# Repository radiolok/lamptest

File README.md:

# lamptest

A modern MCU-based tester for vacuum tubes.

This repository is based on the Polish **AVT5229** vacuum tube tester
("Miernik lamp elektronowych", firmware "VTTester 1.16"). It contains:

* the AVR firmware, ported from the original ICCAVR sources to avr-gcc
* a KiCad 9 redraw of the schematic and PCB, with 3D models
* the original magazine article ([`AVT5229.pdf`](docs/AVT5229.pdf), in Polish) and its [English translation](docs/AVT5229_en.md)

| Top view | Schematic |
|---|---|
|  |  |

## Repository layout

```
firmware/             AVR firmware (C, avr-gcc)
  tests/              host unit tests, with fakes for the hardware
  avt5529.cproj       Atmel Studio 7 project
hardware/             KiCad 9 project: avt.kicad_sch, avt.kicad_pcb
  3d/                 STEP models referenced by the PCB
docs/
  AVT5229.pdf         original article (Polish)
  AVT5229_en.md       English translation
  images/             photos, article figures, PCB renders and diagrams
  diagrams/           diagram sources (make_diagrams.py)
cmake/                avr-gcc toolchain file
```

The PCB refers to the models in `hardware/3d/` as `${KIPRJMOD}/3d/...`, so the
project opens with its 3D view intact from any location. The README diagrams
are drawn by [`docs/diagrams/make_diagrams.py`](docs/diagrams/make_diagrams.py).
After editing it, run `python3 docs/diagrams/make_diagrams.py` to regenerate the
SVGs and the PNGs (it needs `rsvg-convert`, package `librsvg2-bin`).

## What it does

The tester applies the operating voltages from a tube's datasheet. It then
measures the tube's static parameters and its small-signal parameters:

| Quantity | Range | Resolution |
|---|---|---|
| Heater voltage U<sub>h</sub> (or heater current I<sub>h</sub> for series-heated P/U tubes) | 0–15.0 V / 0–2.50 A | 0.1 V / 10 mA |
| Grid bias −U<sub>g1</sub> | 0 … −24.0 V | 0.1 V |
| Anode voltage U<sub>a</sub> | 0–300 V | 1 V |
| Anode current I<sub>a</sub> (auto-range 20 / 200 mA) | 0–200.0 mA | 0.01 / 0.1 mA |
| Screen voltage U<sub>g2</sub> | 0–300 V | 1 V |
| Screen current I<sub>g2</sub> | 0–40.00 mA | 0.01 mA |
| Transconductance S = ΔI<sub>a</sub>/ΔU<sub>g1</sub> | 0–99.9 mA/V | 0.1 |
| Internal resistance R = ΔU<sub>a</sub>/ΔI<sub>a</sub> | 0–99.9 kΩ | 0.1 |
| Amplification factor K = S·R | 0–99.9 | 0.1 |

### Measurement sequence

The sequence runs in 250 ms ticks, driven by `TIMER2_COMP_vect`:

1. Switch on the heater, then wait out the warm-up time (1–9 min, set per tube).
2. Make U<sub>g1</sub> slightly more negative than U<sub>g</sub> (11 ADC steps, about 0.4 V), then ramp up U<sub>a</sub> and U<sub>g2</sub>. Read I<sub>a</sub> and U<sub>g1</sub>.
3. Make U<sub>g1</sub> the same amount less negative than U<sub>g</sub>, and read I<sub>a</sub> and U<sub>g1</sub> again. This gives **S**.
4. Return U<sub>g1</sub> to U<sub>g</sub>. Read I<sub>a</sub> at U<sub>a</sub> − 10 V and at U<sub>a</sub> + 10 V. This gives **R**, and **K** = S·R.
5. Latch the results on the LCD and send them over RS-232.
6. Ramp down U<sub>g2</sub>, U<sub>a</sub> and U<sub>g1</sub>, beep, and switch off the heater.

Press the knob to start a measurement. While the results are on screen, press it
again to re-measure without waiting for warm-up. Turn the knob to abort a
measurement or leave the results screen, which switches off the heater.

### Protections

* **Heater overcurrent**: the heater is switched off (`H` on the LCD).
* **Anode overcurrent** on the 200 mA range: U<sub>a</sub> and U<sub>g2</sub> are switched off (`A`).
* **Screen overcurrent**: U<sub>g2</sub> is switched off (`G`).
* **Heatsink over-temperature** (LM35 sensor): trips above 80 °C, clears below 70 °C (`T`).
* Any error aborts the measurement and sounds the buzzer.
* The watchdog timeout is about 1 s.

## Hardware

* **MCU**: ATmega32 with a 16 MHz crystal. The schematic symbol is the pin-compatible ATmega16A-P.
* **Display**: 4×20 HD44780 LCD in 4-bit mode.
* **Input**: rotary encoder with a push button, and a buzzer.
* **Heater supply**: a PWM step-down converter from the +15 V rail (OC0 → TC4426 → IRF9540N, 1 mH inductor, 1N5822). It runs in voltage mode, or in current mode for series-heater tubes.
* **U<sub>a</sub> and U<sub>g2</sub>**: two linear series regulators fed from a +335 V rail. A filtered PWM signal (OC1B, OC1A) sets the voltage, an LM358 drives an IRF740 pass transistor, and a BD139 limits the current. Their currents are measured on the high side with an LM358 and an MPSA94.
* **U<sub>g1</sub>**: negative bias from a charge pump, clocked by the MCU (`CKUG1`) through a TC4426. It is regulated sample-by-sample in the ADC ISR.
* **Relays**: one relay switches between anode sections (A1/A2). Another switches the I<sub>a</sub> shunt (20/200 mA).
* **Power**: a +15 V rail with a 10 000 µF reservoir capacitor, and an LM317 that makes +5 V for the logic.
* **Interface**: RS-232 through a MAX202, 9600 8N1.

### Block diagram

Blue arrows are control signals from the MCU, labelled with their pins. Dashed
orange arrows are the analog measurements that go to the ADC (port A). The red
tags show which supply rail feeds each block.

### MCU pinout

| Port | 7 | 6 | 5 | 4 | 3 | 2 | 1 | 0 |
|---|---|---|---|---|---|---|---|---|
| **A** (ADC) | U<sub>g1</sub> | I<sub>g2</sub> | U<sub>g2</sub> | I<sub>a</sub> | U<sub>a</sub> | U<sub>h</sub> | I<sub>h</sub> | Temp (LM35) |
| **B** | SCK | MISO | MOSI | K1 | U<sub>h</sub> PWM (OC0) | U<sub>g1</sub> pump clock | Anode select | I<sub>a</sub> range |
| **C** | LCD D7 | LCD D6 | LCD D5 | LCD D4 | LCD E | LCD RS | SDA | SCL |
| **D** | Buzzer (OC2) | Encoder DIR | U<sub>g2</sub> PWM (OC1A) | U<sub>a</sub> PWM (OC1B) | Encoder CLK (INT1) | Encoder button | TXD | RXD |

## Firmware structure

The firmware lives in [`firmware/`](firmware). The logic modules do not touch
the hardware. They reach the outputs through [`hal.h`](firmware/hal.h), which
is inline register code on the AVR and a fake in the host tests.

| File | Contents |
|---|---|
| [`main.c`](firmware/main.c) | Start-up, the main loop and the interrupt vectors, which only call into the modules |
| [`adc_scan.c`](firmware/adc_scan.c) | The 14-step ADC scan: averaging, the U<sub>g1</sub> charge pump, the over-current trips, the U<sub>a</sub>/U<sub>g2</sub> ramps, I<sub>a</sub> auto-range, heater regulation and the over-temperature check |
| [`control.c`](firmware/control.c) | Pure control laws used by the scan: ramp, trip filter, range hysteresis and the heater regulator |
| [`sequencer.c`](firmware/sequencer.c) | The measurement sequence, with named step points, and the S/R/K calculation |
| [`button.c`](firmware/button.c) | Push button debounce: click, held and released |
| [`editor.c`](firmware/editor.c) | Encoder handling: moving the cursor, changing values, switching sections and aborting |
| [`panel.c`](firmware/panel.c) | Main loop work: loads the selected record, converts the readings, saves edits and renders the report line |
| [`ui.c`](firmware/ui.c), [`lcd.c`](firmware/lcd.c) | LCD screens, and the HD44780 driver in 4-bit mode with field blinking |
| [`uart.c`](firmware/uart.c) | Serial output, and the `ESC` request |
| [`convert.c`](firmware/convert.c), [`format.c`](firmware/format.c) | ADC to physical units, S/R/K arithmetic and fixed-point formatting |
| [`lamp.c`](firmware/lamp.c), [`lampdb.c`](firmware/lampdb.c) | The `lamp_t` record and its editable fields; the flash tube table, the EEPROM user table and the last selected slot |
| [`app.c`](firmware/app.c) | State shared between the main loop and the interrupts: set points, errors, the selected tube and the live readings |
| [`config.h`](firmware/config.h), [`board.h`](firmware/board.h) | Thresholds and timing constants; pin assignment and the inline hardware access |
| [`tests/`](firmware/tests) | Host unit tests |

The interrupts do all the real-time work. The main loop only converts the
averaged readings, refreshes the LCD, saves edits to EEPROM and sends reports.

### Measurement sequencer

The sequencer counts down in 250 ms steps. Each action runs at a named
point (`enum seq_point` in [`sequencer.h`](firmware/sequencer.h)). The
diagram shows the outputs and readings against the step number:

## Tube database

**Flash (81 entries, read-only).** Slot `00` is a **bench power supply** mode,
where every voltage can be set by hand. Slot `01` is reserved. Slots `02`–`80`
are preset tubes, with each triode section of a twin triode stored as its own
entry:

ECC81, ECC82, ECC83, ECC85, ECC88, ECC91, ECC99, ECC35, ECC40, ECC801, ECC802, ECC803, ECC832,
E180CC, E182CC, PCC84, PCC85, PCC88, 6N1P, 6N2P, 6N3P, 6N6P, 6N30P, 6N5S, 6N7S, 6SL7, 6SN7, 6SC7,
6AS7, 6S19P, 6S2S, EF86, 6SJ7, EL34, EL84, EL90, EL95, 6V6S, 6F6S, 6L6G, 6P1P, KT66, KT77, KT88,
ECL82, ECL86, PCL86.

**EEPROM (19 entries, slots 81–99, user-editable).** You can edit every field
with the encoder: name, socket, electrode system, warm-up time, every voltage
and current, and the reference values for S, R and K.

Each name has 9 characters: `TTTTTT` `s` `e` `m`.

* `TTTTTT` is the tube type.
* `s` is the socket/adapter letter, A–J.
* `e` is the electrode system: `0` for a single tube, `1` or `2` for a section of a twin tube.
* `m` is the heater warm-up time in minutes.

For example, `ECC83_G11` means ECC83, socket G, section 1, 1 minute warm-up.

## Serial output

Press `ESC` in a terminal at 9600 8N1 to get a copy of the LCD. The tester
also sends a line automatically after every measurement:

```
Nr Type Uh[V] Ih[mA] -Ug[V] Ua[V] Ia[mA] Ug2[V] Ig2[mA] S[mA/V] R[k] K[V/V]
```

## Building the firmware

You need CMake ≥ 3.16 and the avr-gcc toolchain. On Debian or Ubuntu, install
`gcc-avr`, `binutils-avr` and `avr-libc`.

```sh
cmake -B build            # the AVR toolchain file is picked automatically
cmake --build build
```

The build writes these files to `build/firmware/`:

* `avt5229.hex`: the flash image
* `avt5229.eep`: the EEPROM image, with the user tube table
* `avt5229.elf` and `avt5229.map`

It also prints the memory usage. To treat warnings as errors, add `-DWERROR=ON`.

The Atmel Studio 7 project (`firmware/avt5529.cproj`) is still there for Windows users.

### Unit tests

The logic modules also build for the PC, with fakes for the hardware and for
`<avr/pgmspace.h>` and `<avr/eeprom.h>`. The tests run with AddressSanitizer
and UndefinedBehaviorSanitizer. You need a host C compiler and CMake:

```sh
cmake -B build-tests -DLAMPTEST_TESTS=ON
cmake --build build-tests
ctest --test-dir build-tests --output-on-failure
```

The tests cover:

* **Golden checks.** Every unit conversion, the S/R/K arithmetic and the heater
  regulator are compared, exhaustively or over millions of inputs, with
  verbatim copies of the original formulas ([`tests/legacy.h`](firmware/tests/legacy.h)).
* **ADC scan.** A simulated free-running ADC checks the channel order,
  the averaging, the U<sub>g1</sub> pump, the trips, the ramps, auto-range and over-temperature.
* **Sequencer.** A full measurement on a model triode checks the step order,
  the S/R/K results, the beeps, hold, re-measure, abort and errors.
* **User interface.** The button debounce, cursor movement and value limits,
  section switching, EEPROM saves, power-supply mode, and the exact report line.
* **Tube database.** Every record is valid, and every twin-tube section 1 is
  followed by its section 2.

GitHub Actions builds the firmware and runs the unit tests on every push and
pull request ([.github/workflows/build.yml](.github/workflows/build.yml)).
The `.hex`, `.eep`, `.elf` and `.map` files are uploaded as build artifacts.

Ready-made firmware is on the [Releases](https://github.com/radiolok/lamptest/releases) page:

* **`latest`**: a pre-release rebuilt from every push to `master`
  ([`avt5229.hex`](https://github.com/radiolok/lamptest/releases/download/latest/avt5229.hex),
  [`avt5229.eep`](https://github.com/radiolok/lamptest/releases/download/latest/avt5229.eep)).
* **`v*`**: a permanent release for every version tag, e.g. `git tag v1.0 && git push origin v1.0`.

### Flashing

The fuse values are listed in `board.h`:

* **Low fuse 0xEF**: external crystal, BOD off.
* **High fuse 0xC9**: JTAG off, which is required because PORTC drives the LCD. SPI programming stays on, and CKOPT is set.

```sh
avrdude -c usbasp -p m32 -U lfuse:w:0xEF:m -U hfuse:w:0xC9:m
avrdude -c usbasp -p m32 -U flash:w:build/firmware/avt5229.hex:i \
                         -U eeprom:w:build/firmware/avt5229.eep:i
```

> **Note:** writing `.eep` replaces your user-defined tubes (slots 81–99) with
> the defaults.

## Firmware fixes in this port

These bugs were found and fixed while bringing the avr-gcc port up:

| Problem | Effect | Fix |
|---|---|---|
| `tick_1ms` and `uart_busy`, which are set from ISRs, were not `volatile` | `-Os` turned `delay()` and `char2rs()` into endless loops. The firmware hung after start-up and the watchdog reset it about once a second. The compiler had even dropped the rest of `main()` as unreachable. | Make the ISR-shared flags `volatile` |
| `eeprom_read_block()` had its arguments swapped, copied from the ICCAVR call order | Selecting a user tube (slot ≥ 81) copied EEPROM data over the CPU registers and I/O space | Fix the argument order |
| `eeprom_write_word()` was used on 1-byte fields (name, U<sub>g1</sub>, U<sub>h</sub>, I<sub>h</sub>) | Editing one field zeroed the next one. For example, saving U<sub>g1</sub> cleared the low byte of U<sub>a</sub>, and saving the warm-up time cleared U<sub>h</sub>. | Use `eeprom_write_byte()` |
| `poptyp` (the last selected tube) was a RAM variable, but it was accessed with the EEPROM API | Every measurement wrote to the EEPROM address equal to its RAM address, which corrupted user tube slot 86 | Store it in the EEPROM byte right after the user table, which keeps the table layout. Add a range check and use `eeprom_update_byte()`. |
| The refactored `fp2ascii()` never advanced past the `'.'`, and it blanked *every* `0` in the integer part | Displayed values were wrong (`12.6` → `126`, `100` → `1  `) and the LCD fields were misaligned | Rewrite it to match the original formatting, and check it on the host |
| `temp_str[]` was defined in a header; prototypes were missing | Link error with `-fno-common` (GCC ≥ 10) and implicit-declaration warnings | Move it into `fp2ascii()` and add the prototypes |

### Refactoring

The original single 1500-line source was split into the modules listed in
[Firmware structure](#firmware-structure), and all comments were translated
into English. The behaviour is unchanged, except for these fixes:

| Change | Why |
|---|---|
| The sequencer step, the warm-up time, the ADC averages and the power-supply set points are read and written with interrupts blocked | A 16-bit value shared with an interrupt could be torn |
| S is reported as 99.9 when ΔU<sub>g</sub> = 0 | It was a division by zero |
| The LCD enable pulse lasts 8 cycles (500 ns) | `RJMP .+2` skipped every other delay, which made the pulse about 310 ns, under the HD44780 minimum of 450 ns |
| EEPROM edits use `eeprom_update_*()` | Saving an unchanged value no longer wears the EEPROM |
| The last selected slot is a member of the EEPROM layout, with a default of 0 | Its address no longer depends on a cast. The `.eep` image is one byte longer, and the user table is byte-identical. |
| The two lookup tables are stored in flash | Saves 150 bytes of RAM. The firmware now uses 10.1 kB of flash (was 12.5 kB) and 514 bytes of RAM (was 550). |

### Known limitations (not changed)

* S and R use unsigned differences. If noise makes I<sub>a</sub> go the wrong way between the two readings, the result wraps around and shows as nonsense.
* Power-supply mode shows `* OVERHEAT Warning *` on the last line, as in the original firmware.

## Links

* AVT5229 kit (PCB + programmed MCU): <https://sklep.avt.pl/miernik-lamp-elektronowych-plytka-drukowana-i-zaprogramowany-uklad.html>

## License

MIT. See [LICENSE](LICENSE). The original AVT5229 design and firmware belong to their authors and AVT.

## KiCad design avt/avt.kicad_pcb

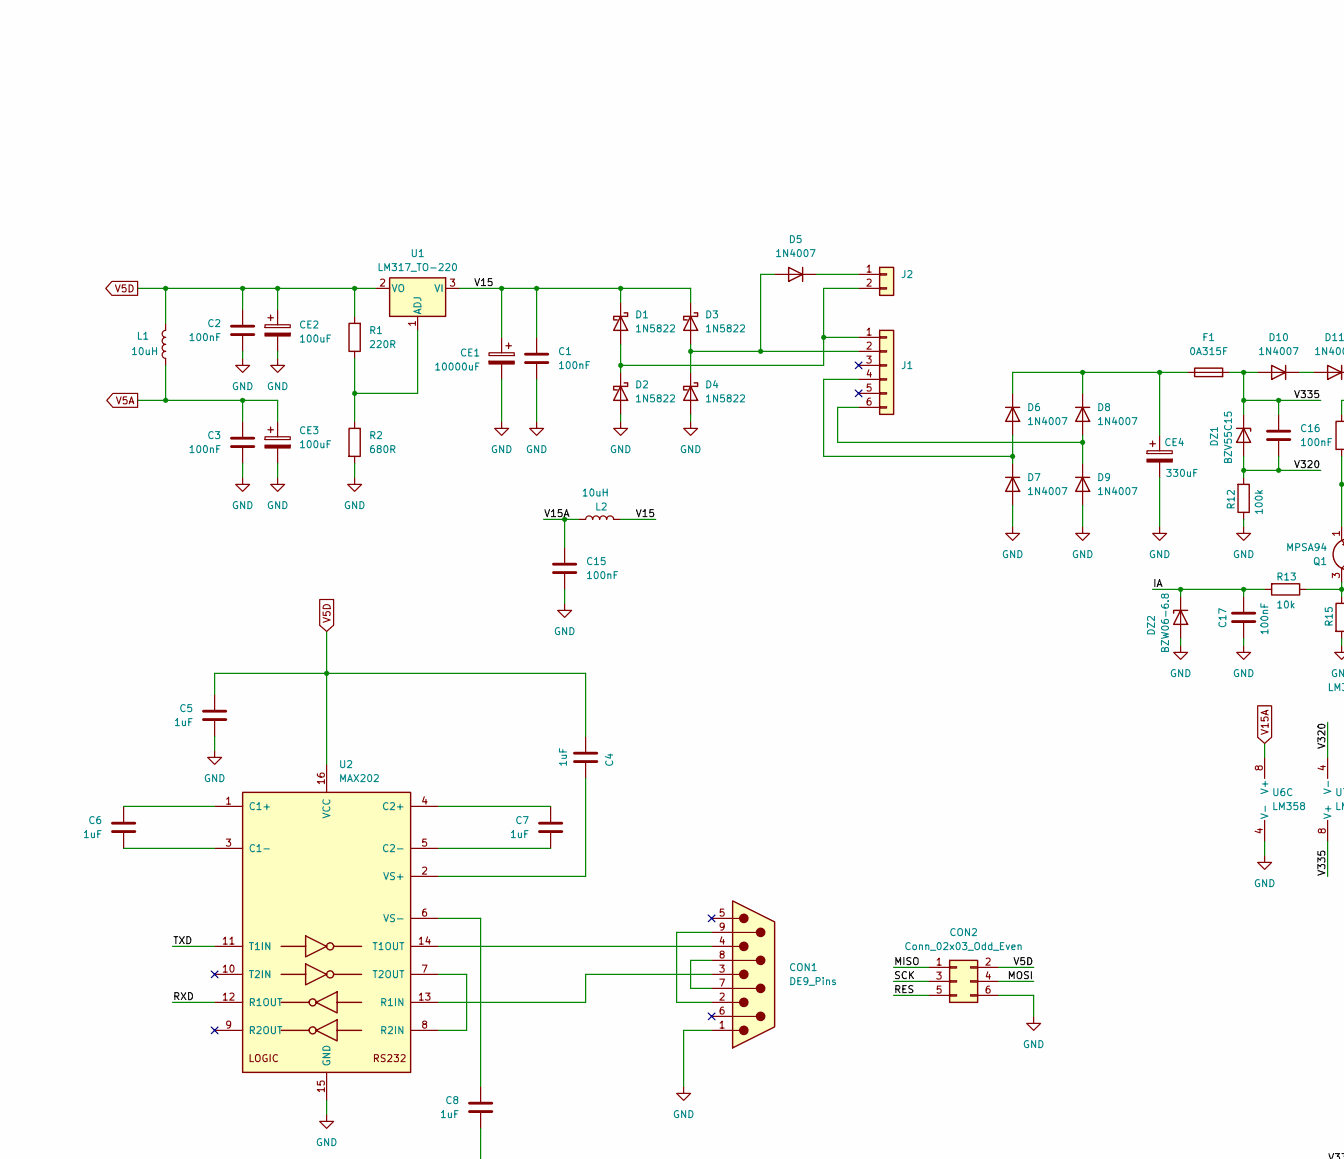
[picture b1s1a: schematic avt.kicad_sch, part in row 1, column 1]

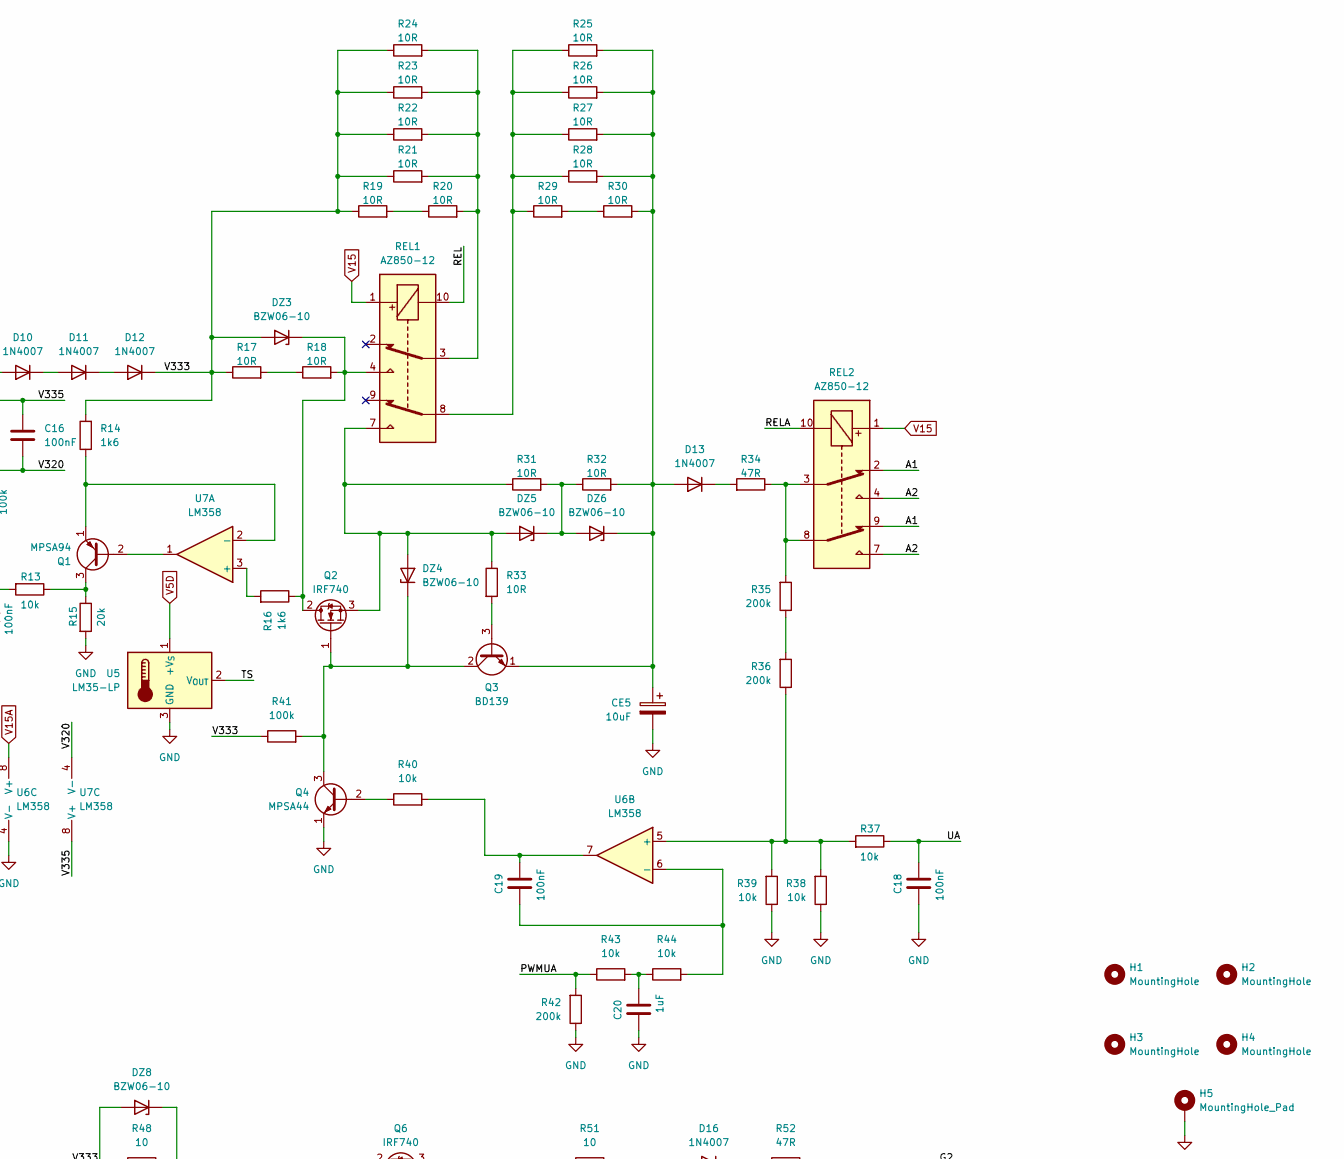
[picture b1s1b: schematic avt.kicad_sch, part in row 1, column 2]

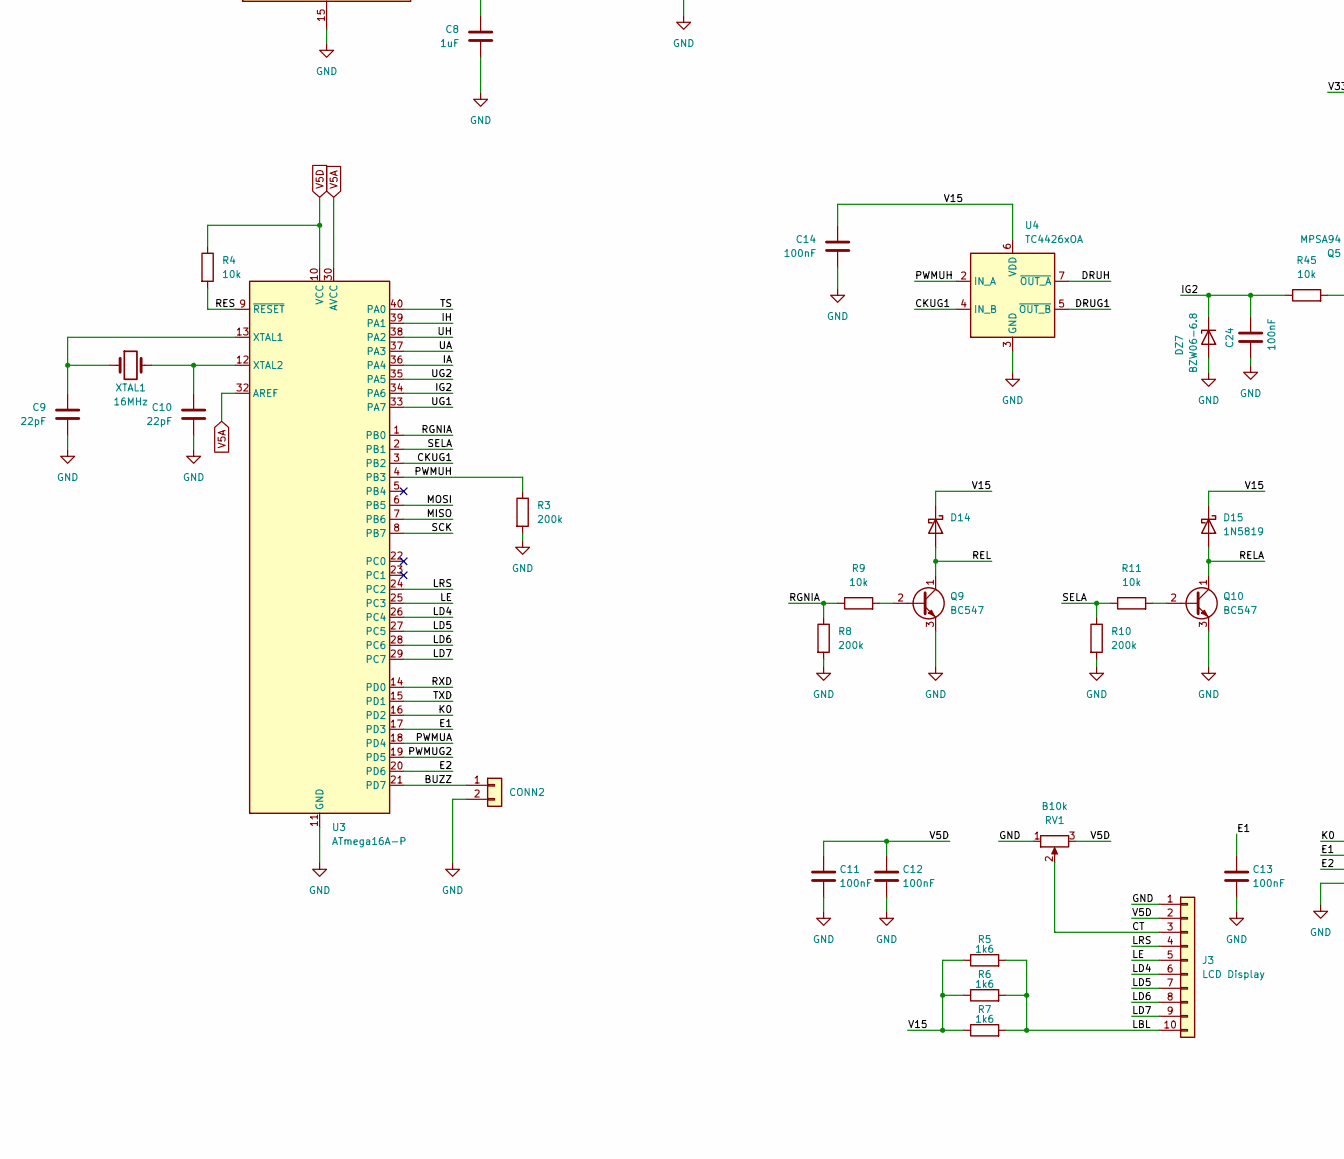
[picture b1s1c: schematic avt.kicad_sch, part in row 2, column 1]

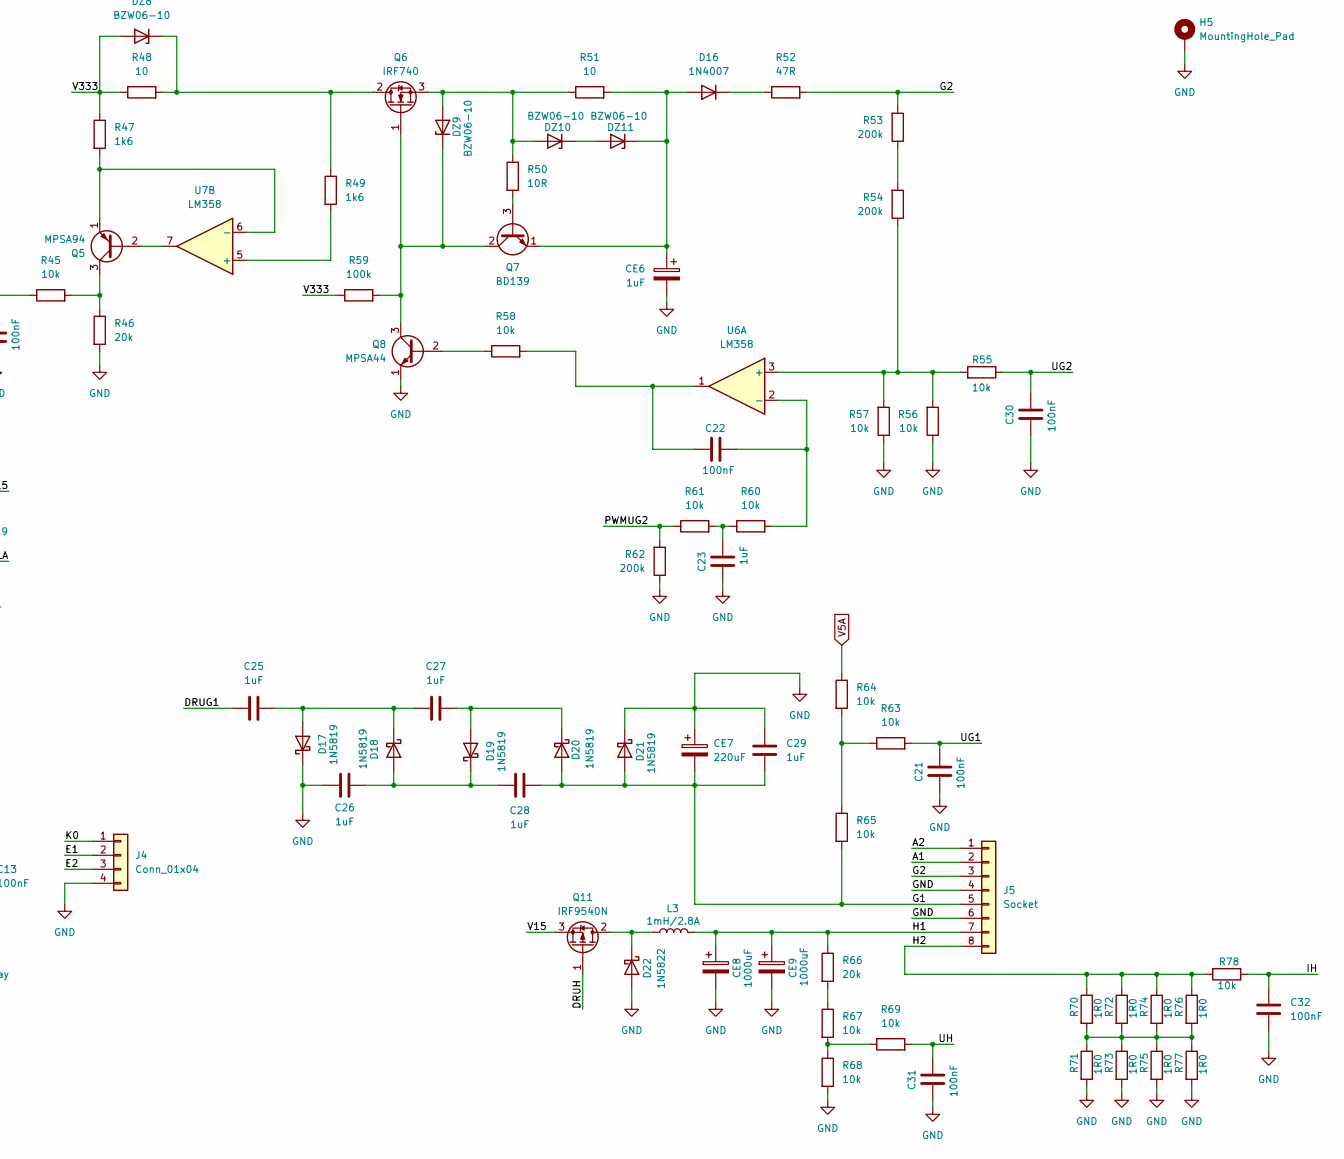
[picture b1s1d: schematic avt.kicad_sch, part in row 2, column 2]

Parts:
C1, C2, C3, C11, C12, C13, C14, C15, C16, C17, C18, C19, C21, C22, C24, C30, C31, C32: 100nF; C_1206_3216Metric
C4, C5, C6, C7, C8, C20, C23, C29: 1uF; C_1206_3216Metric
C9, C10: 22pF; C_1206_3216Metric
C25, C26, C27, C28: 1uF; C_Disc_D7.5mm_W2.5mm_P5.00mm
CE1: 10000uF; CP_Radial_D30.0mm_P10.00mm_SnapIn
CE2, CE3: 100uF; CP_Radial_D5.0mm_P2.50mm
CE4: 330uF; CP_Radial_D35.0mm_P10.00mm_SnapIn
CE5: 10uF; CP_Radial_D10.0mm_P5.00mm
CE6: 1uF; CP_Radial_D10.0mm_P5.00mm
CE7: 220uF; CP_Radial_D6.3mm_P2.50mm
CE8, CE9: 1000uF; CP_Radial_D10.0mm_P5.00mm
CON1: DE9_Pins; DSUB-9_Pins_Horizontal_P2.77x2.84mm_EdgePinOffset9.90mm_Hou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
CON2: Conn_02x03_Odd_Even; PinHeader_2x03_P2.54mm_Vertical
CONN2: Conn_01x02; PinHeader_1x02_P2.54mm_Vertical
D1, D2, D3, D4, D22: 1N5822; D_DO-201AD_P15.24mm_Horizontal
D5, D6, D7, D8, D9, D10, D11, D12, D13, D16: 1N4007; D_DO-41_SOD81_P7.62mm_Horizontal
D14: D_DO-41_SOD81_P7.62mm_Horizontal
D15, D17, D18, D19, D20, D21: 1N5819; D_DO-41_SOD81_P7.62mm_Horizontal
DZ1: BZV55C15; D_DO-41_SOD81_P7.62mm_Horizontal
DZ2, DZ7: BZW06-6.8; D_DO-41_SOD81_P7.62mm_Horizontal
DZ3, DZ4, DZ5, DZ6, DZ8, DZ9, DZ10, DZ11: BZW06-10; D_DO-41_SOD81_P7.62mm_Horizontal
F1: 0A315F; Fuseholder_Cylinder-5x20mm_Stelvio-Kontek_PTF78_Horizontal_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
H1, H2, H3, H4: MountingHole; MountingHole_5.3mm_M5
H5: MountingHole_Pad; MountingHole_3.2mm_M3_ISO7380_Pad_TopBottom
J1: Conn_01x06; TE_826576-6_1x06_P3.96mm_Vertical
J2: Conn_01x02; Molex_KK-254_AE-6410-02A_1x02_P2.54mm_Vertical
J3: LCD Display; JST_XH_B10B-XH-A_1x10_P2.50mm_Vertical
J4: Conn_01x04; Molex_KK-254_AE-6410-04A_1x04_P2.54mm_Vertical
J5: Socket; JST_VH_B8P-VH_1x08_P3.96mm_Vertical
L1, L2: 10uH; L_Toroid_Horizontal_D6.5mm_P10.00mm_Diameter7-5mm_Amidon-T25
L3: 1mH/2.8A; L_Toroid_Vertical_L31.8mm_W15.9mm_P13.50mm_Bourns_5700
Q1, Q5: MPSA94; TO-92S_Wide
Q2, Q6: IRF740; TO-220-3_Vertical
Q3, Q7: BD139; TO-126-3_Vertical
Q4, Q8: MPSA44; TO-92S_Wide
Q9, Q10: BC547; TO-92S_Wide
Q11: IRF9540N; TO-220-3_Vertical
R1: 220R; R_1206_3216Metric
R2: 680R; R_1206_3216Metric
R3, R8, R10, R35, R36, R42, R53, R54, R62: 200k; R_1206_3216Metric
R4, R9, R11, R13, R37, R38, R39, R40, R43, R44, R45, R55, R56, R57, R58, R60, R61, R63, R64, R65, R67, R68, R69, R78: 10k; R_1206_3216Metric
R5, R6, R7, R14, R16, R47, R49: 1k6; R_1206_3216Metric
R12, R41, R59: 100k; R_Axial_Power_L25.0mm_W9.0mm_P10.16mm_Vertical
R15, R46, R66: 20k; R_1206_3216Metric
R17, R18, R19, R20, R21, R22, R23, R24, R25, R26, R27, R28, R29, R30, R31, R32, R33, R50: 10R; R_1206_3216Metric
R34, R52: 47R; R_Axial_Power_L25.0mm_W9.0mm_P10.16mm_Vertical
R48, R51: 10; R_1206_3216Metric
R70, R71, R72, R73, R74, R75, R76, R77: 1R0; R_1206_3216Metric
REL1, REL2: AZ850-12; Relay_DPDT_FRT5
RV1: B10k; Potentiometer_Bourns_3386F_Vertical
U1: LM317_TO-220; TO-220-3_Vertical
U2: MAX202; DIP-16_W7.62mm
U3: ATmega16A-P; DIP-40_W15.24mm
U4: TC4426xOA; SOIC-8_3.9x4.9mm_P1.27mm
U5: LM35-LP; TO-92S_Wide
U6, U7: LM358; SOIC-8_3.9x4.9mm_P1.27mm
XTAL1: 16MHz; Crystal_HC18-U_Vertical

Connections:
/A1: J5.2, REL2.2, REL2.9
/A2: J5.1, REL2.4, REL2.7
/BUZZ: CONN2.1, U3.21 (PD7)
/CKUG1: U3.3 (PB2), U4.4 (IN_B)
/CT: J3.3, RV1.2
/DRUG1: C25.1, U4.5 (~OUT_B)
/DRUH: Q11.1 (G), U4.7 (~OUT_A)
/E1: C13.1, J4.2, U3.17 (PD3)
/E2: J4.3, U3.20 (PD6)
/G1: C28.2, C29.2, CE7.2, D20.2 (A), D21.2 (A), J5.5, R65.2
/G2: J5.3, R52.2, R53.2
/H1: CE8.1, CE9.1, J5.7, L3.1, R66.1
/H2: J5.8, R70.1, R72.1, R74.1, R76.1, R78.2
/IA: C17.1, DZ2.1 (K), R13.2, U3.36 (PA4)
/IG2: C24.1, DZ7.1 (K), R45.1, U3.34 (PA6)
/IH: C32.1, R78.1, U3.39 (PA1)
/K0: J4.1, U3.16 (PD2)
/LBL: J3.10, R5.2, R6.2, R7.2
/LD4: J3.6, U3.26 (PC4)
/LD5: J3.7, U3.27 (PC5)
/LD6: J3.8, U3.28 (PC6)
/LD7: J3.9, U3.29 (PC7)
/LE: J3.5, U3.25 (PC3)
/LRS: J3.4, U3.24 (PC2)
/MISO: CON2.1, U3.7 (PB6)
/MOSI: CON2.4, U3.6 (PB5)
/PWMUA: R42.2, R43.1, U3.18 (PD4)
/PWMUG2: R61.1, R62.2, U3.19 (PD5)
/PWMUH: R3.1, U3.4 (PB3), U4.2 (IN_A)
/REL: D14.2 (A), Q9.1 (C), REL1.10
/RELA: D15.2 (A), Q10.1 (C), REL2.10
/RES: CON2.5, R4.2, U3.9 (~RESET)
/RGNIA: R8.1, R9.1, U3.1 (PB0)
/RXD: U2.12 (R1OUT), U3.14 (PD0)
/SCK: CON2.3, U3.8 (PB7)
/SELA: R10.1, R11.1, U3.2 (PB1)
/TS: U3.40 (PA0), U5.2 (V_{OUT})
/TXD: U2.11 (T1IN), U3.15 (PD1)
/UA: C18.1, R37.1, U3.37 (PA3)
/UG1: C21.1, R63.2, U3.33 (PA7)
/UG2: C30.1, R55.1, U3.35 (PA5)
/UH: C31.1, R69.2, U3.38 (PA2)
/V320: C16.2, DZ1.2 (A), R12.2, U7.4 (V-)
/V333: D12.1 (K), DZ3.2 (A), DZ8.2 (A), R14.2, R17.1, R19.1, R21.1, R22.1, R23.1, R24.1, R41.1, R47.1, R48.1, R59.1
/V335: C16.1, D10.2 (A), DZ1.1 (K), F1.2, U7.8 (V+)
GND: C1.2, C2.2, C3.2, C5.2, C8.2, C9.2, C10.2, C11.2, C12.2, C13.2, C14.2, C15.2, C17.2, C18.2, C20.2, C21.2, C23.2, C24.2, C26.1, C29.1, C30.2, C31.2, C32.2, CE1.2, CE2.2, CE3.2, CE4.2, CE5.2, CE6.2, CE7.1, CE8.2, CE9.2, CON1.0, CON1.1, CON2.6, CONN2.2, D2.2 (A), D4.2 (A), D7.2 (A), D9.2 (A), D17.1 (K), D21.1 (K), D22.2 (A), DZ2.2 (A), DZ7.2 (A), H5.1, J3.1, J4.4, J5.4, J5.6, Q4.1 (E), Q8.1 (E), Q9.3 (E), Q10.3 (E), R2.2, R3.2, R8.2, R10.2, R12.1, R15.2, R38.1, R39.1, R42.1, R46.2, R56.1, R57.1, R62.1, R68.2, R71.2, R73.2, R75.2, R77.2, RV1.1, U2.15 (GND), U3.11 (GND), U3.31 (GND), U4.3 (GND), U5.3 (GND), U6.4 (V-)
unnamed: C19.1, R40.2, U6.7
unnamed: C20.1, R43.2, R44.1
unnamed: C22.2, R58.2, U6.1
unnamed: C23.1, R60.1, R61.2
unnamed: CON1.2, CON1.9
unnamed: CON1.7, CON1.8
unnamed: D1.2 (A), D2.1 (K), J1.1, J2.2
unnamed: D3.2 (A), D4.1 (K), D5.2 (A), J1.2
unnamed: D5.1 (K), J2.1
unnamed: D6.2 (A), D7.1 (K), J1.4
unnamed: CE4.1, D6.1 (K), D8.1 (K), F1.1
unnamed: D8.2 (A), D9.1 (K), J1.6
unnamed: D10.1 (K), D11.2 (A)
unnamed: D11.1 (K), D12.2 (A)
unnamed: CE5.1, D13.2 (A), DZ6.1 (K), Q3.1 (E), R25.2, R26.2, R27.2, R28.2, R30.2, R32.2
unnamed: D13.1 (K), R34.2
unnamed: CE6.1, D16.2 (A), DZ11.1 (K), Q7.1 (E), R51.2
unnamed: D16.1 (K), R52.1
unnamed: C25.2, C27.1, D17.2 (A), D18.1 (K)
unnamed: C26.2, C28.1, D18.2 (A), D19.1 (K)
unnamed: C27.2, D19.2 (A), D20.1 (K)
unnamed: D22.1 (K), L3.2, Q11.2 (D)
unnamed: DZ3.1 (K), Q2.2 (D), R16.1, R18.2, REL1.4
unnamed: DZ4.2 (A), DZ5.2 (A), Q2.3 (S), R31.1, R33.1, REL1.7
unnamed: DZ4.1 (K), Q2.1 (G), Q3.2 (C), Q4.3 (C), R41.2
unnamed: DZ5.1 (K), DZ6.2 (A), R31.2, R32.1
unnamed: DZ8.1 (K), Q6.2 (D), R48.2, R49.1
unnamed: DZ9.1 (K), Q6.1 (G), Q7.2 (C), Q8.3 (C), R59.2
unnamed: DZ9.2 (A), DZ10.2 (A), Q6.3 (S), R50.1, R51.1
unnamed: DZ10.1 (K), DZ11.2 (A)
unnamed: Q1.2 (B), U7.1
unnamed: Q1.3 (C), R13.1, R15.1
unnamed: Q1.1 (E), R14.1, U7.2 (-)
unnamed: Q3.3 (B), R33.2
unnamed: Q4.2 (B), R40.1
unnamed: Q5.2 (B), U7.7
unnamed: Q5.3 (C), R45.2, R46.1
unnamed: Q5.1 (E), R47.2, U7.6 (-)
unnamed: Q7.3 (B), R50.2
unnamed: Q8.2 (B), R58.1
unnamed: Q9.2 (B), R9.2
unnamed: Q10.2 (B), R11.2
unnamed: R17.2, R18.1
unnamed: R19.2, R20.1
unnamed: R20.2, R21.2, R22.2, R23.2, R24.2, REL1.3
unnamed: R25.1, R26.1, R27.1, R28.1, R29.1, REL1.8
unnamed: R29.2, R30.1
unnamed: R34.1, R35.2, REL2.3, REL2.8
unnamed: R35.1, R36.2
unnamed: R53.1, R54.2
unnamed: R63.1, R64.2, R65.1
unnamed: R66.2, R67.1
unnamed: R67.2, R68.1, R69.1
unnamed: R70.2, R71.1, R72.2, R73.1, R74.2, R75.1, R76.2, R77.1
unnamed: R1.1, R2.1, U1.1 (ADJ)
unnamed: C6.1, U2.1 (C1+)
unnamed: C6.2, U2.3 (C1-)
unnamed: C7.1, U2.4 (C2+)
unnamed: C7.2, U2.5 (C2-)
unnamed: CON1.3, U2.13 (R1IN)
unnamed: U2.7 (T2OUT), U2.8 (R2IN)
unnamed: CON1.4, U2.14 (T1OUT)
unnamed: C4.2, U2.2 (VS+)
unnamed: C8.1, U2.6 (VS-)
unnamed: C9.1, U3.13 (XTAL1), XTAL1.1
unnamed: C10.1, U3.12 (XTAL2), XTAL1.2
unnamed: R54.1, R55.2, R56.2, R57.2, U6.3 (+)
unnamed: C22.1, R60.2, U6.2 (-)
unnamed: R36.1, R37.2, R38.2, R39.2, U6.5 (+)
unnamed: C19.2, R44.2, U6.6 (-)
unnamed: R16.2, U7.3 (+)
unnamed: R49.2, U7.5 (+)
V5A: C3.1, CE3.1, L1.2, R64.1, U3.30 (AVCC), U3.32 (AREF)
V5D: C2.1, C4.1, C5.1, C11.1, C12.1, CE2.1, CON2.2, J3.2, L1.1, R1.2, R4.1, RV1.3, U1.2 (VO), U2.16 (VCC), U3.10 (VCC), U5.1 (+V_{S})
V15: C1.1, C14.1, CE1.1, D1.1 (K), D3.1 (K), D14.1 (K), D15.1 (K), L2.1, Q11.3 (S), R5.1, R6.1, R7.1, REL1.1, REL2.1, U1.3 (VI), U4.6 (VDD)
V15A: C15.1, L2.2, U6.8 (V+)

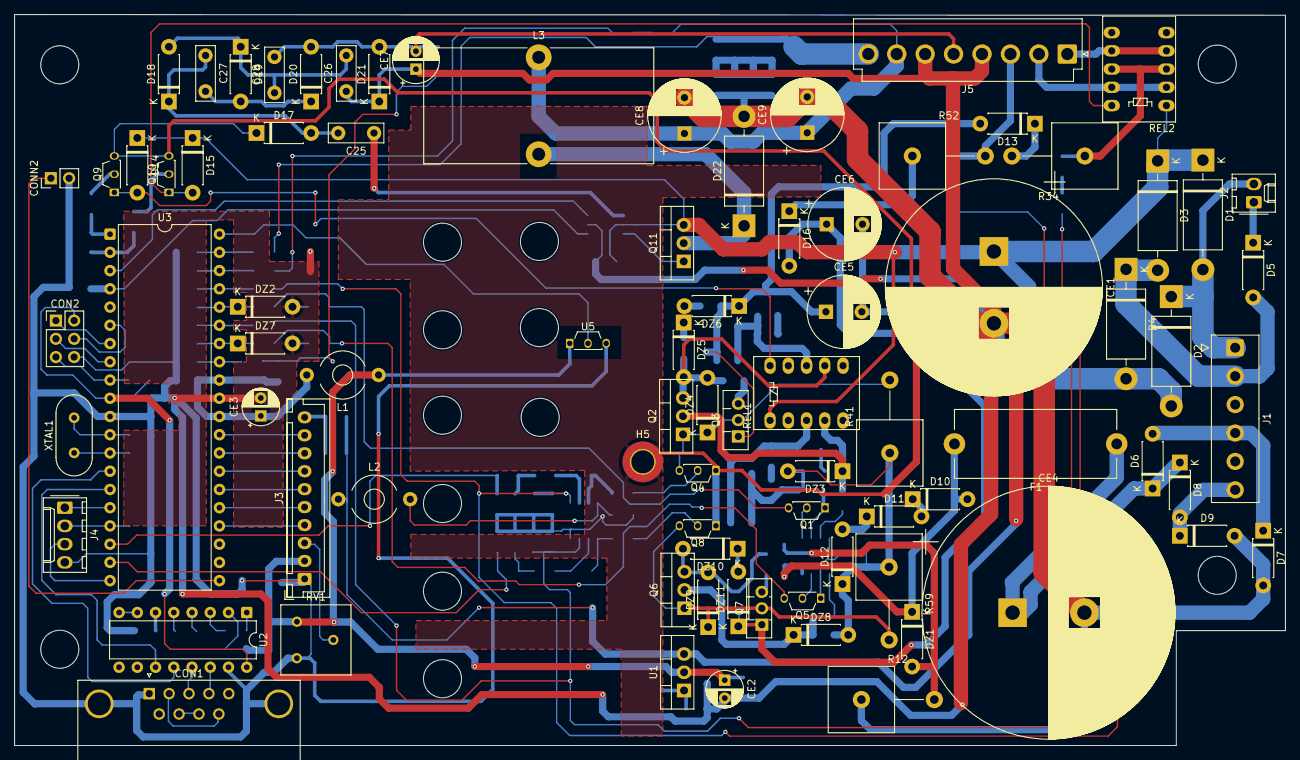
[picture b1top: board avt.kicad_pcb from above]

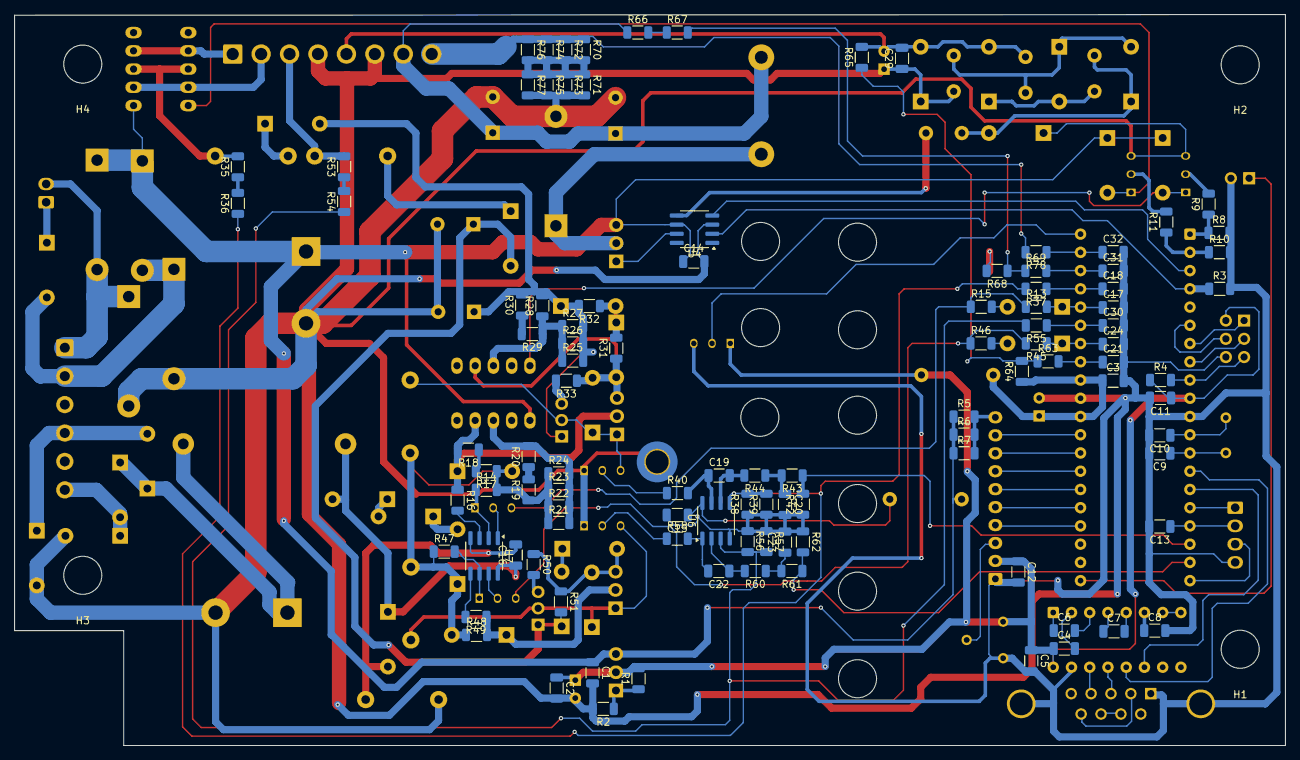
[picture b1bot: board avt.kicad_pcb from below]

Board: 2 copper layers, 177.0 x 101.8 mm, 191 parts (108 on the bottom side), 122 nets.

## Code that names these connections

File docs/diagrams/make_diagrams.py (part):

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    s.block(20, 30, 180, 96, "ui", ["Power supply", "+335 V anode rail", "+15 V rail",
                                    "LM317 → +5 V logic"])
    ui = [
        (165, ["LCD 4×20", "HD44780, 4-bit"], "PC2–PC7", "out"),
        (255, ["Rotary encoder", "with push button"], "PD2,3,6", "in"),
        (345, ["Buzzer"], "PD7", "out"),
        (415, ["RS-232", "MAX202 → DE-9"], "PD0,1", "both"),
        (505, ["LM35", "heatsink temp."], "ADC0", "meas"),
    ]
    MX, MW = 290, 140
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                                       "PWM step-down, voltage or current mode",
                                       "TC4426 · IRF9540N · 1 mH · 1N5822"])
    s.pill(B + full - 40, 150, "+15 V")
    ctrl(172, B, "PB3 · OC0 PWM")
    meas([(B, 214), (R, 214)], "ADC1 I_{h} · ADC2 U_{h}", 214)
    to_tube(B + full, 191, "H")

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                                       "Negative charge pump, regulated per sample",
                                       "TC4426"])
    s.pill(B + full - 40, 270, "+15 V")
    ctrl(292, B, "PB2 · pump clock")
    meas([(B, 334), (R, 334)], "ADC7 U_{g1}", 334)
    to_tube(B + full, 311, "G1")

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    s.block(B2, 400, BW, 82, "anode", ["I_{a} sense", "high side", "LM358 · MPSA94"])
    s.block(B3, 400, 130, 82, "anode", ["Anode select", "relay", "A1 / A2"])
    s.block(B2, 530, BW, 56, "anode", ["I_{a} range relay", "20 / 200 mA shunt"])
    ctrl(420, B, "PD4 · OC1B PWM")
    s.poly([(B + BW, 441), (B2, 441)], WIRE, sw=2.4)
    s.poly([(B2 + BW, 441), (B3, 441)], WIRE, sw=2.4)
    s.poly([(B2 + 140, 482), (B2 + 140, 530)], WIRE, sw=2.4, end=False)
    meas([(B2 + 40, 482), (B2 + 40, 508), (R, 508)], "ADC3 U_{a} · ADC4 I_{a}", 508)
    ctrl(558, B2, "PB0 · I_{a} range")
    s.poly([(R, 620), (B3 + 65, 620), (B3 + 65, 482)], CTRL)
    s.text(R + 8, 614, "PB1 · anode select", 12, 400, fill=CTRL)
    to_tube(B3 + 130, 426, "A1")
    to_tube(B3 + 130, 458, "A2")

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                                       "LM358 · IRF740 · BD139"])
    s.pill(B + BW - 40, 670, "+335 V")
    s.block(B2, 670, BW, 82, "screen", ["I_{g2} sense", "high side", "LM358 · MPSA94"])
    ctrl(690, B, "PD5 · OC1A PWM")
    s.poly([(B + BW, 711), (B2, 711)], WIRE, sw=2.4)
    meas([(B2 + 40, 752), (B2 + 40, 778), (R, 778)], "ADC5 U_{g2} · ADC6 I_{g2}", 778)
    to_tube(B2 + BW, 711, "G2")
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
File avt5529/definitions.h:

#ifndef DEFINITIONS_H
#define DEFINITIONS_H

#include <avr/io.h>
#include <avr/eeprom.h>
#include <avr/pgmspace.h>
#include <avr/interrupt.h>

//*************************************************************
//                           TESTER
//*************************************************************
// OCD  JTAG SPI CK  EE   BOOT BOOT BOOT BOD   BOD SU SU CK   CK   CK   CK
// EN    EN  EN  OPT SAVE SZ1  SZ0  RST  LEVEL EN  T1 T0 SEL3 SEL2 SEL1 SEL0
//  1     0   0   1   1    0    0    1    1     1   1  0  0    0    0    1
//  1     1   0   0   1    0    0    1    1     1   1  0  1    1    1    1
//    ICCAVR = 0xc9ef
//*************************************************************

#define BIT(x)  (1<<(x))
#define LOW(x)  ((char)((int)(x)))
#define HIGH(x) ((char)(((int)(x))>>8))
#define ESC     '\033'
#define WDR     __asm("WDR")
#define SEI     __asm("SEI")
#define CLI     __asm("CLI")
#define NOP     __asm("NOP")
#define NOP2    __asm("RJMP .+2")

#define SET200  PORTB |= BIT(0)          // ustaw zakres 200mA
#define RST200  PORTB &= ~BIT(0)          // ustaw zakres 20mA

#define SETSEL  PORTB |= BIT(1)                   // ustaw UA1
#define RSTSEL  PORTB &= ~BIT(1)                  // ustaw UA2

#define ENSET   PORTC |= BIT(3)                // ustaw ENABLE
#define ENRST   PORTC &= ~BIT(3)               // kasuj ENABLE
#define RSSET   PORTC |= BIT(2)                   // ustaw R\S
#define RSRST   PORTC &= ~BIT(2)                  // kasuj R\S

#define DUSK0   ( PIND & BIT(2) ) == 0        // K0 nacisniety

#define RIGHT   ( PIND & BIT(6) ) == 0        // obrot w prawo

#define TOPPWM  ICR1                      // gorna granica PWM
#define PWMUG2  OCR1A                               // PWM Ug2
#define PWMUA   OCR1B                                // PWM Ua
#define PWMUH   OCR0                                // 8bit Uh

#define SPKON   TCCR2 |= BIT(COM20)               // wlacz ton
#define SPKOFF  TCCR2 &= ~BIT(COM20)             // wylacz ton

#define CLKUG1SET PORTB |= BIT(2)              // ustaw CLKUG1
#define CLKUG1RST PORTB &= ~BIT(2)             // kasuj CLKUG1

#define KWARC   16000000               // czestotliwosc kwarcu
#define RATE    103                              // 9600,N,8,1
#define MS1     250                      // podstawa czasu 1ms
#define MRUG    250                      // taktowanie migania
#define DMIN    20                          // czas drgan 20ms
#define DMAX    250                        // czas drgan 250ms
#define LPROB   63            // liczba usrednianych probek 64

#define HITEMP  10240         // 80"C = 0.8V/5.12V * 1024 * 64
#define LOTEMP  8960          // 70"C = 0.7V/5.12V * 1024 * 64

#define OVERSAMP 2              // liczba probek do alarmu - 1
#define OVERIH  0b00000001                // znacznik bledu IH
#define OVERIA  0b00000010                // znacznik bledu IA
#define OVERIG  0b00000100               // znacznik bledu IG2
#define OVERTE  0b00001000     // znacznik wzrostu temperatury

#define ADRREZ  0b00000000                // adres REZ w ADMUX
#define ADRIH   0b00000001                 // adres IH w ADMUX
#define ADRUH   0b00000010                 // adres UH w ADMUX
#define ADRUA   0b00000011                 // adres UA w ADMUX
#define ADRIA   0b00000100                 // adres IA w ADMUX
#define ADRUG2  0b00000101                // adres UG2 w ADMUX
#define ADRIG2  0b00000110                // adres IG2 w ADMUX
#define ADRUG1  0b00000111                // adres UG1 w ADMUX

#define TMAR    2
//      tuh     *240
#define TUA     8
#define TUG2    8
#define TUG     16
#define TUH     8

#define FUA     2
#define FUG2    2
#define FUG     2
#define FUH     2
#define BIP     4

#endif

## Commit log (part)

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2020-07-07 Add data about AVT5229 project
2020-07-07 Add notice
2023-12-30 Updated to Atmel Studio 7.0
2024-01-05 refactor fp2ascii
2024-01-14 fix compilation issue
